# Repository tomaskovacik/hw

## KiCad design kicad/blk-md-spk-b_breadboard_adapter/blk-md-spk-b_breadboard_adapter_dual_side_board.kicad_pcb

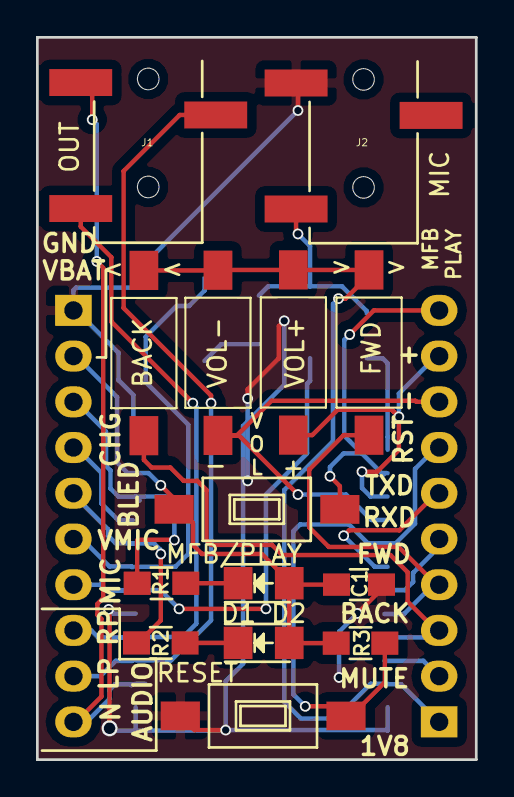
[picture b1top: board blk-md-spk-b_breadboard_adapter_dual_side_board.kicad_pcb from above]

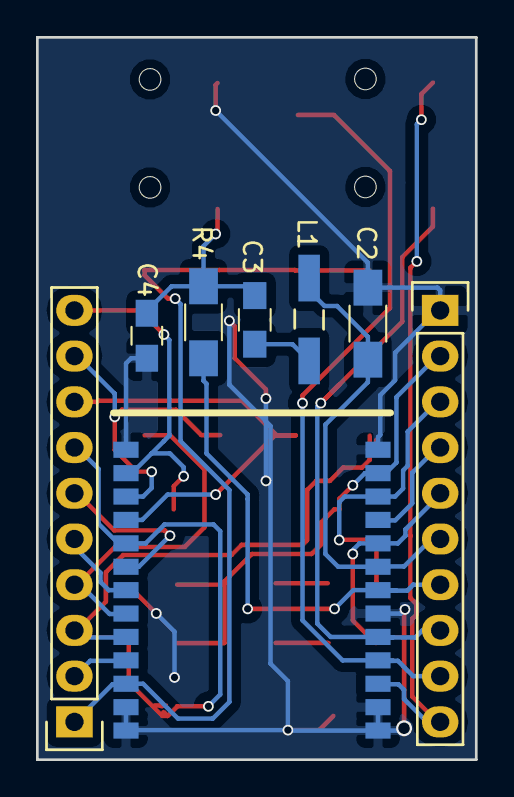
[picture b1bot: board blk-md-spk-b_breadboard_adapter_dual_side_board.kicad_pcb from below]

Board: 2 copper layers, 24.4 x 40.1 mm, 22 parts (8 on the bottom side), 24 nets.

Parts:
BACK: SW_PUSH; SW_SPST_FSMSM
C1: 100n; C_0805_HandSoldering
C2: 4u7; C_1206_HandSoldering
C3: 1u; C_1206_HandSoldering
C4: 10; C_0805_HandSoldering
D1, D2: LED; LED-1206
FWD: SW_PUSH; SW_SPST_FSMSM
J1, J2: Jack_3.5mm_3pin; 3.5mm_stereo_jack_PJ320B
L1: 15n; Choke_SMD_1206_Handsoldering
MFB/PLAY: SW_PUSH; SW_SPST_FSMSM
P1, P2: CONNECTOR; Pin_Header_Straight_1x10
R1, R2: 470; R_0805_HandSoldering
R3: 10k; R_0805_HandSoldering
R4: 2k7; R_0805_HandSoldering
RESET: SW_PUSH; SW_SPST_FSMSM
U1: BLK-MD-SPK-B; BLK-MD-SPK-B_no_up_silk
VOL+: SW_PUSH; SW_SPST_FSMSM
VOL-: SW_PUSH; SW_SPST_FSMSM

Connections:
/1V8: BACK.2, FWD.2, P1.1, U1.24, VOL+.2, VOL-.2
/BACK: BACK.1, P1.3, U1.22
/BLED: P2.5, R2.2, U1.9
/CHG: P2.4, U1.10
/FWD: FWD.1, P1.4, U1.21
/MFB: MFB/PLAY.1, P1.10, U1.15
/MIC: C3.2, P2.7, U1.7
/MUTE: P1.2, U1.23
/RLED: P2.3, R1.2, U1.11
/RST: P1.7, R3.1, RESET.1, U1.18
/RXD: P1.5, U1.20
/SPKLP: J1.3, P2.9, U1.4
/SPKN: J1.1, P2.10, U1.3
/SPKRP: J1.2, P2.8, U1.5
/TXD: P1.6, U1.19
/VBAT: C1.2, D1.2, D2.2, MFB/PLAY.2, P2.2, R3.2, U1.12
/VMIC: C2.1, L1.2, P2.6, U1.8
/VOL+: P1.9, U1.16, VOL+.1
/VOL-: P1.8, U1.17, VOL-.1
GND: C1.1, C2.2, C4.2, J2.1, P2.1, RESET.2, U1.1, U1.2, U1.6, U1.13, U1.14, U1.25, U1.26
unnamed: C3.1, C4.1, J2.2, R4.2
unnamed: D1.1, R1.1
unnamed: D2.1, R2.1
unnamed: L1.1, R4.1

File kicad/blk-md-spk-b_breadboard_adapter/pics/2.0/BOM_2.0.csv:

"Id";"Designator";"Package";"Quantity";"Designation";"Supplier and ref";
1;"RESET,MFB/PLAY,BACK,FWD,VOL+,VOL-";"SW_SPST_FSMSM";6;"SW_PUSH";;;
2;"J1,J2";"3.5mm_stereo_jack_PJ320B";2;"Jack_3.5mm_3pin";;;
3;"P2,P1";"Pin_Header_Straight_1x10";2;"CONNECTOR";;;
4;"U1";"BLK-MD-SPK-B_no_up_silk";1;"BLK-MD-SPK-B";;;
5;"R2,R1";"R_0805_HandSoldering";2;"470";;;
6;"D2,D1";"LED-1206";2;"LED";;;
7;"C1";"C_0805_HandSoldering";1;"100n";;;
8;"R3";"R_0805_HandSoldering";1;"10k";;;
9;"C2";"C_1206_HandSoldering";1;"4u7";;;
10;"C3";"C_1206_HandSoldering";1;"1u";;;
11;"C4";"C_0805_HandSoldering";1;"10";;;
12;"L1";"Choke_SMD_1206_Handsoldering";1;"15n";;;
13;"R4";"R_0805_HandSoldering";1;"2k7";;;

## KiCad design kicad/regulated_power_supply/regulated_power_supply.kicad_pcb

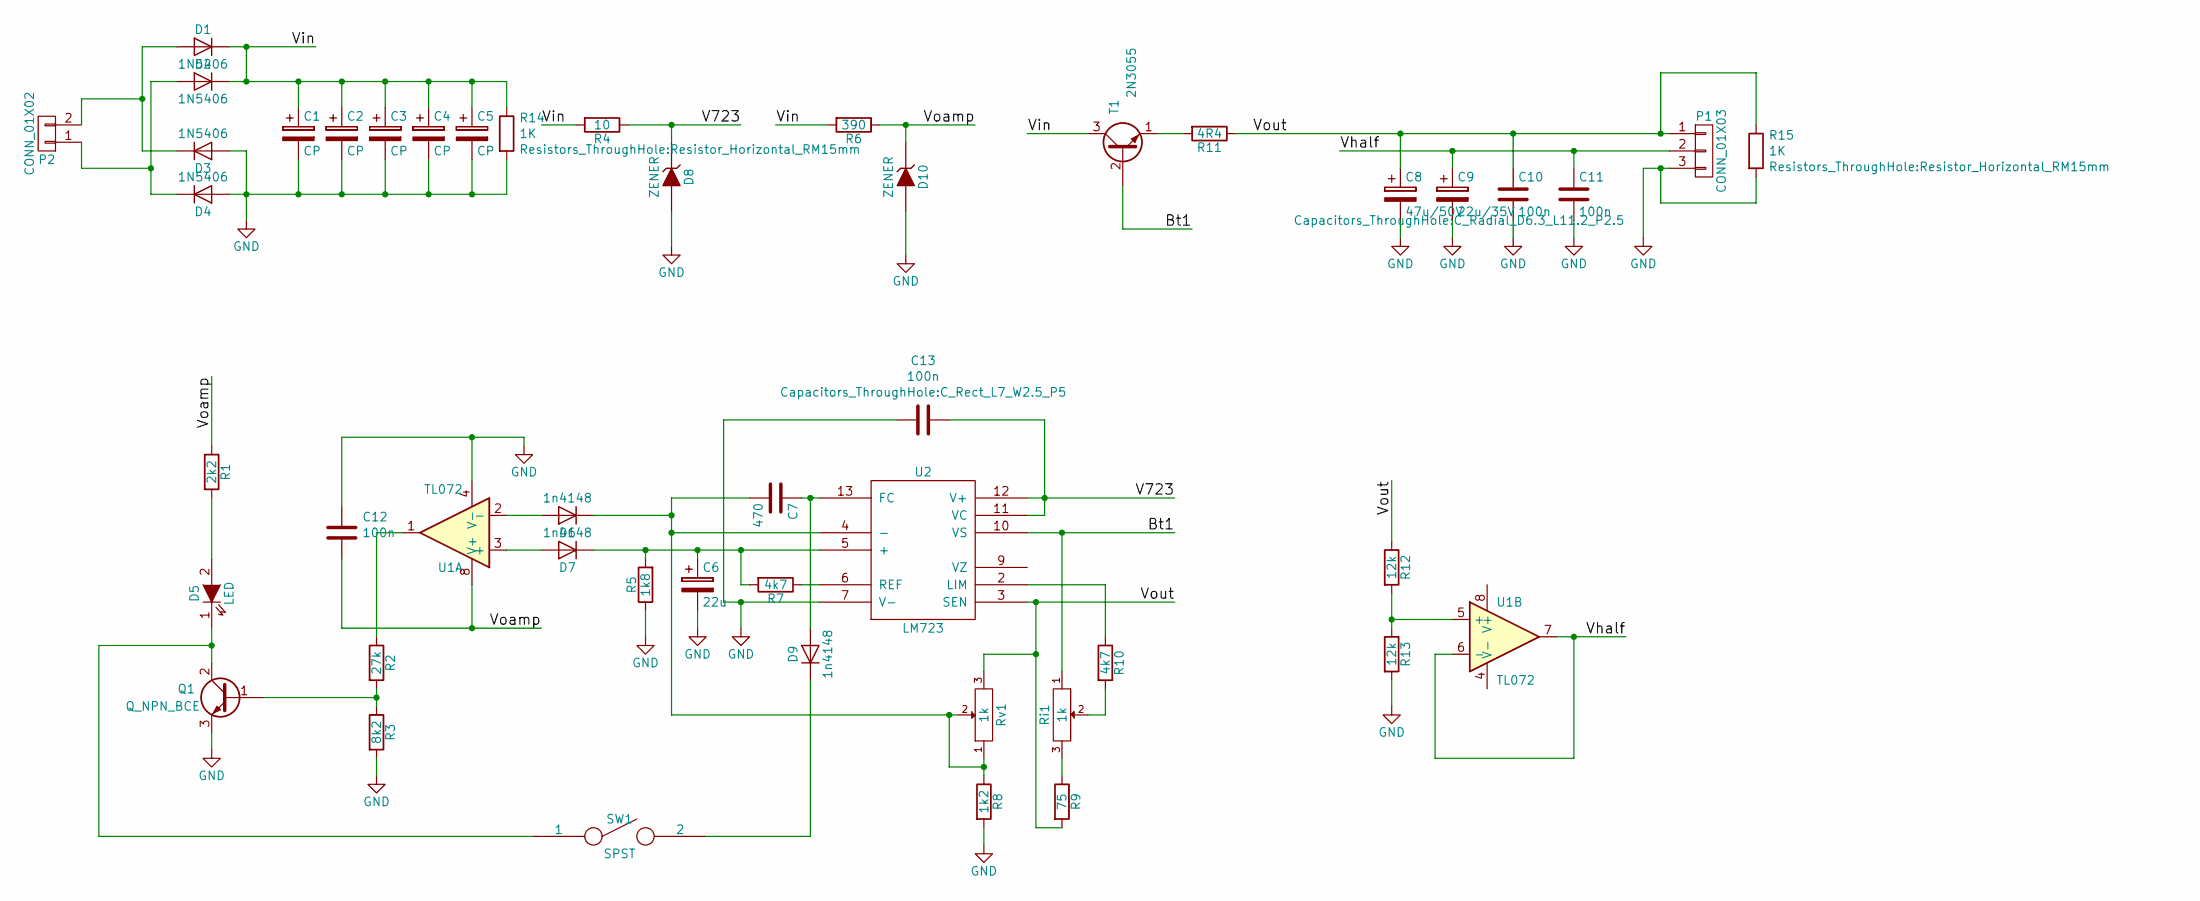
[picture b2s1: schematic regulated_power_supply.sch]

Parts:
C1, C2, C3, C4, C5: CP; C_Radial_D18_L36_P7.5
C6: 22u; C_Radial_D6.3_L11.2_P2.5
C7: 470; C_Rect_L7_W2_P5
C8: 47u/50V; C_Radial_D6.3_L11.2_P2.5
C9: 22u/35V; C_Radial_D6.3_L11.2_P2.5
C10, C11: 100n; C_Rect_L7_W2_P5
C12, C13: 100n; C_Rect_L7_W2.5_P5
D1, D2, D3, D4: 1N5406; Diode_DO-201AD_Horizontal_RM15
D5: LED; LED-5MM
D6, D7, D9: 1n4148; Diode_DO-35_SOD27_Horizontal_RM10
D8, D10: ZENER; Diode_DO-35_SOD27_Horizontal_RM10
P1: CONN_01X03; Pin_Header_Straight_1x03
P2: CONN_01X02; Pin_Header_Straight_1x02
Q1: Q_NPN_BCE; TO-92_Inline_Narrow_Oval
R1: 2k2; Resistor_Horizontal_RM10mm
R2: 27k; Resistor_Horizontal_RM10mm
R3: 8k2; Resistor_Horizontal_RM10mm
R4: 10; Resistor_Horizontal_RM10mm
R5: 1k8; Resistor_Horizontal_RM10mm
R6: 390; Resistor_Horizontal_RM10mm
R7: 4k7; Resistor_Horizontal_RM10mm
R8: 1k2; Resistor_Horizontal_RM10mm
R9: 75; Resistor_Horizontal_RM15mm
R10: 4k7; Resistor_Horizontal_RM15mm
R11: 4R4; Resistor_Horizontal_RM30mm
R12, R13: 12k; Resistor_Horizontal_RM10mm
R14, R15: 1K; Resistor_Horizontal_RM15mm
Ri1: 1k; Pin_Header_Straight_1x03
Rv1: 1k; Pin_Header_Straight_1x03
SW1: SPST; Pin_Header_Straight_1x02
T1: 2N3055; Pin_Header_Straight_1x03
U1: TL072; DIP-8_W7.62mm_LongPads
U2: LM723; DIP-14_W7.62mm_LongPads

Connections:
/Bt1: Ri1.1, T1.2 (B), U2.10 (VS)
/V723: C13.1, D8.1 (K), R4.1, U2.11 (VC), U2.12 (V+)
/Vhalf: C9.1, C11.1, P1.2, U1.6 (-), U1.7
/Vin: C1.1, C2.1, C3.1, C4.1, C5.1, D1.1 (K), D2.1 (K), R4.2, R6.2, R14.1, T1.3 (C)
/Voamp: C12.2, D10.1 (K), R1.1, R6.1, U1.8 (V+)
/Vout: C8.1, C10.1, P1.1, R9.2, R11.1, R12.1, R15.1, Rv1.3, U2.3 (SEN)
GND: C1.2, C2.2, C3.2, C4.2, C5.2, C6.2, C8.2, C9.2, C10.2, C11.2, C12.1, C13.2, D3.2 (A), D4.2 (A), D8.2 (A), D10.2 (A), P1.3, Q1.3 (E), R3.2, R5.1, R8.2, R13.2, R14.2, R15.2, U1.4 (V-), U2.7 (V-)
unnamed: C6.1, D7.1 (K), R5.2, R7.2, U2.5 (+)
unnamed: C7.1, D9.2 (A), U2.13 (FC)
unnamed: C7.2, D6.1 (K), R8.1, Rv1.1, Rv1.2, U2.4 (-)
unnamed: D1.2 (A), D3.1 (K), P2.2
unnamed: D2.2 (A), D4.1 (K), P2.1
unnamed: D5.1 (K), Q1.2 (C), SW1.1
unnamed: D5.2 (A), R1.2
unnamed: D6.2 (A), U1.2 (-)
unnamed: D7.2 (A), U1.3 (+)
unnamed: D9.1 (K), SW1.2
unnamed: Q1.1 (B), R2.2, R3.1
unnamed: R2.1, U1.1
unnamed: R7.1, U2.6 (REF)
unnamed: R9.1, Ri1.3
unnamed: R10.1, U2.2 (LIM)
unnamed: R10.2, Ri1.2
unnamed: R11.2, T1.1 (E)
unnamed: R12.2, R13.1, U1.5 (+)

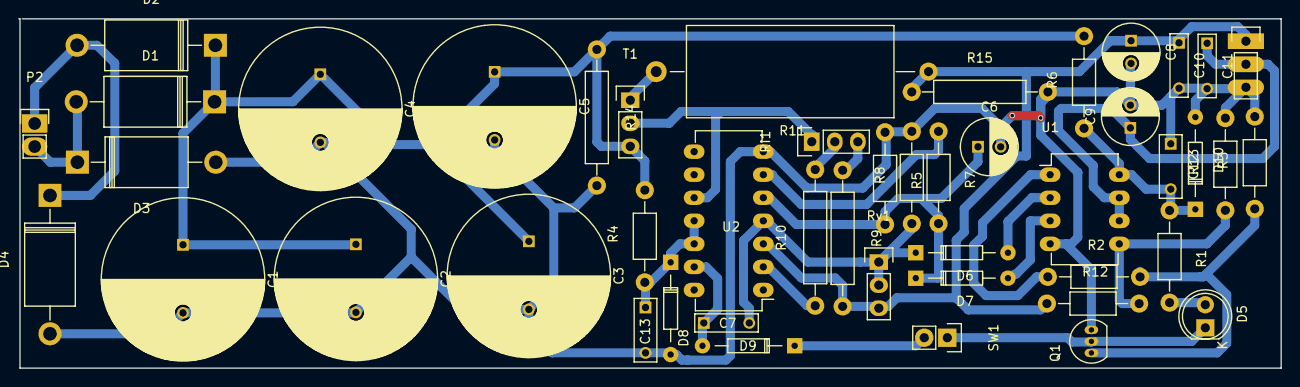
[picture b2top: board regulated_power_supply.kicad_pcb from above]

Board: 2 copper layers, 139.1 x 38.5 mm, 47 parts (0 on the bottom side), 25 nets.

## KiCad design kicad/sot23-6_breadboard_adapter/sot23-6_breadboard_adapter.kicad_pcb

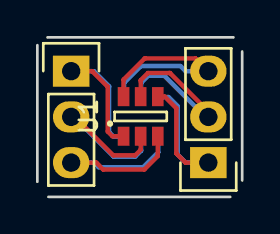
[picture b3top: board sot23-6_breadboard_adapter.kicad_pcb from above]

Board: 2 copper layers, 11.4 x 8.9 mm, 4 parts (1 on the bottom side), 6 nets.

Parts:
P1, P2: CONN_01X03; Pin_Header_Straight_1x03
U1, U2: MCP3421A0T-E/CH; SOT-23-6

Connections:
unnamed: P1.1, U1.1, U2.3
unnamed: P1.2, U1.2, U2.2
unnamed: P1.3, U1.3, U2.1
unnamed: P2.1, U1.4, U2.6
unnamed: P2.2, U1.5, U2.5
unnamed: P2.3, U1.6, U2.4
